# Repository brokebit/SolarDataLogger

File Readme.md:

# This repo has submodules
- To clone: git clone --recurse-submodules -j8 REPO_URL
- To pull latest versin: git pull --recurse-submodules

# What is all this

Firmware for custom data logger for Victron MPPT charge controllers via the Ve.Direct port/protocol.

## Features
- Power via 9v-20v input or USB
- ESP32-C6 RISC-V CPU
- Wifi 6 support and provisioning credentials via BLE
- Receive, parse, and publish data from a Victron MPPT controller
- Publishes: panel voltage, battery voltage, panel current, battery current, serial number, etc
- Publish data via MQTT in InfluxDB line protocol format
- Onboard temperature and humidity sensors (AHT20)
- Support for optional add on board with current sensor (INA226) and solid state relay (CMX60D10)
- WS2812 LED for status information
- CP2102N USB Uart for programing and logging
- USB port direct to ESP32-C6
- Remote control via MQTT command channel

## Supported Victron MPPT Controllers

Supports both the smaller MPPT controllers that have load output and control:

- MPPT 75/10
- MPPT 75/15
- MPPT 100/10
- MPPT 100/20

Also support larger MPPT controllers without load output via a INA226 Current sensor on an add-on board:

- MPPT 100/30
- MPPT 100/50
- MPPT 150/35
- MPPT 150/45
- MPPT 150/60
- MPPT 250/70

## The Details
This is a Platform IO project. Last tested with ESP IDF 5.3.1

- /lib contains drivers and victron parser
- /src contains main program

Edit platform.ini to set some global variables and config parameters. 
- INA226_PRESENT: Set this to one if you have a INA226 connected. Otherwise 0. 
- AHT20_PRESENT: Set this to 1 if you have a AHT20 connected. Otherwise 0.
- SENSOR_LOCATION: Set this to any string you want. It will be included in the mqtt message. No more than 24 characters
- SENSOR_TYPE: Set this to whatever you want. i.e. ESP32-C6 or ESP32-S3. No more than 24 characters

# MQTT

## Channels
- Influx data is sent to MQTT_TOPIC
- Command should be submitted to the channel named mac address + "-cmd" i.e. FFEEDDCCBBAA-cmd 
- Commands responses are sent to the channel named mac address. i.e. FFEEDDCCBBAA

## Support remote MQTT Commands
- ota - Perform an OTA Update
- rbk - Roll back to previous version 
- rst - Reboot
- png - Get a pong back
- tmp - Get current temp in C
- hum - Get current humidity
- mem - Get free heap memory
- ver - Get firmware version

# OTA
- Firmware is download via https from any URL. The firmware looks for a file that is the mac address in all caps. 
- Firmware URL is defined in : OTA_BASE_URL (without the filename)
- Rememeber you need to configure partitions.csv 1mb partition is not enough. 

# WiFi Provisioning
- To make a QR Code for provisioning use the following JSON string and fill in appropriate values:
```{"ver":"v1","name":"PROV_123456","pop":"abcd12345","transport":"ble"}```
- Use the mobile app called "ESP BLE Provisioning"
- In menuconfig make sure that: Component config -> Bluetooth -> Bluetooth controller -> Controller Options is set to BLE not Dual Mode.

# What can you do with it? 

## Grafana Dashboard Example

# To Do
- Fix math for INA226 current sensor and address twos compliment
- CMX60D10 Relay Driver
- Some way to configure it without recompiling 
- Redo design in KiCad instead of EasyEDA and add to repo
- Finish add onboard with INA226 and CMX60D10
- Code clean up. Comments, proper error handling, review memory managment, null point checks, etc
- Add remote commands for reading voltage and current data
- MQTT TLS Support

# Done
- WS2812 Driver
- OTA Updates
- Wifi Provisioning via BLE

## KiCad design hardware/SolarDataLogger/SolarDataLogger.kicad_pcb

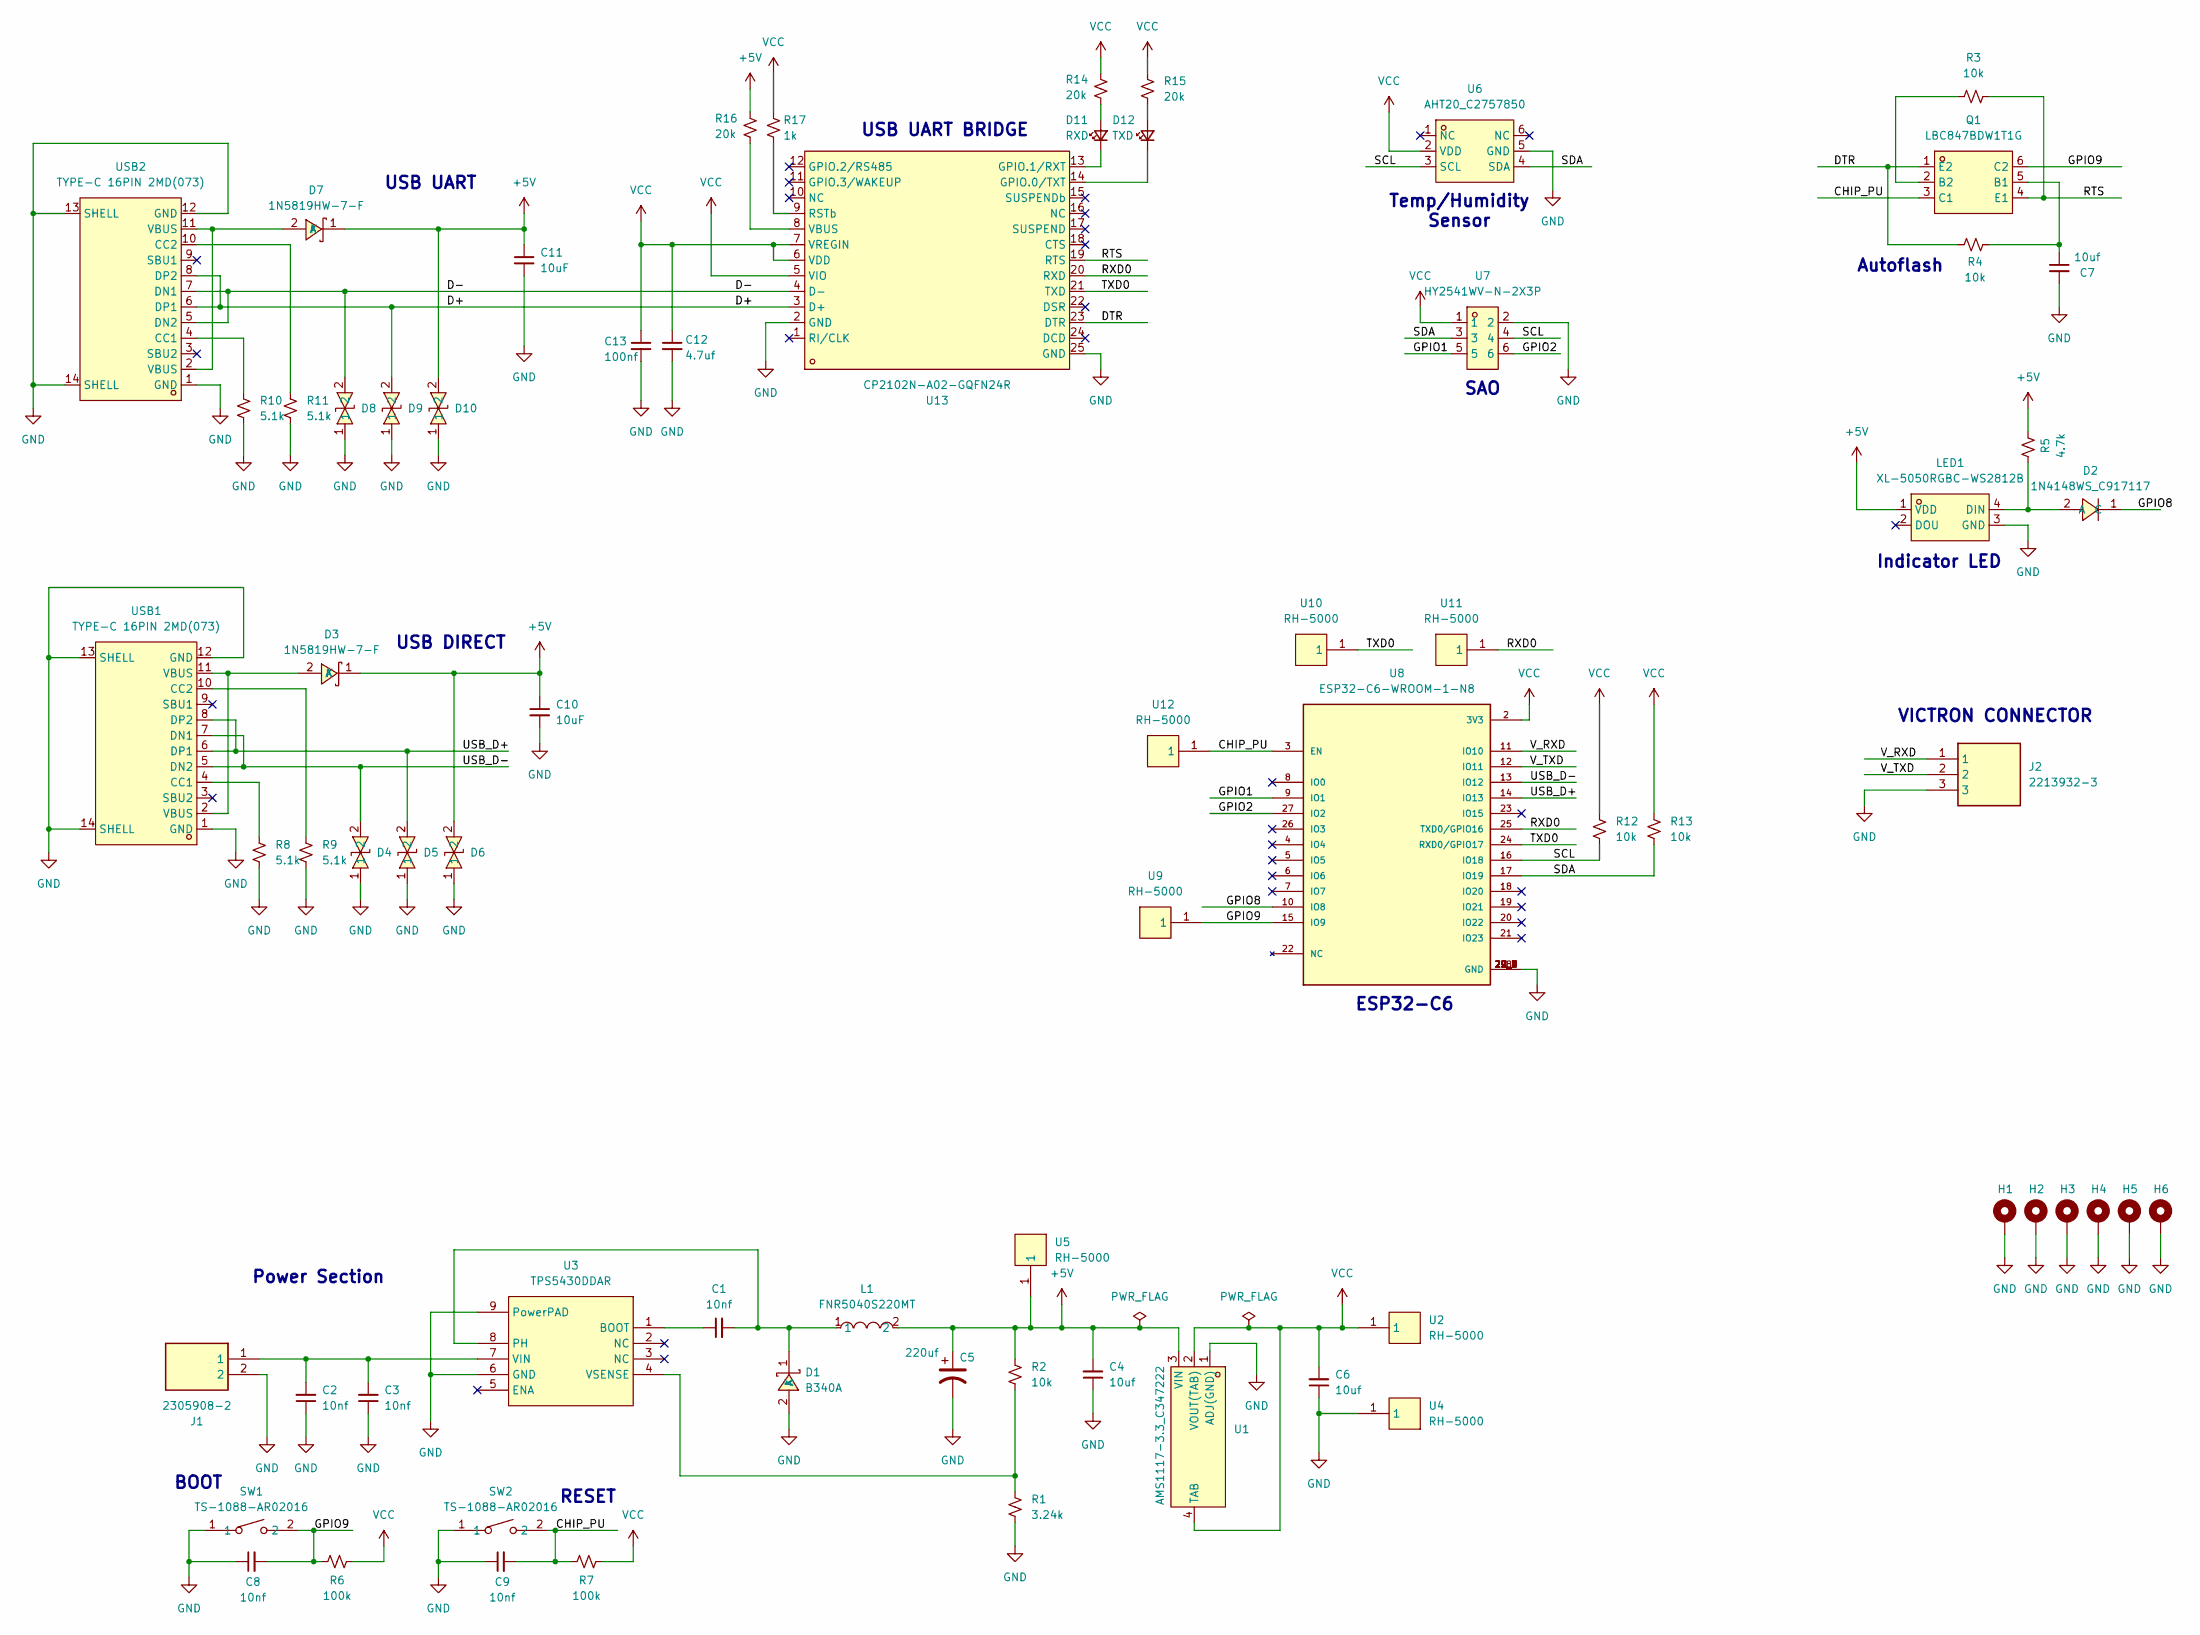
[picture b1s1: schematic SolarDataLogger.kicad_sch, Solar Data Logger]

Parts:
C1, C2, C3, C8, C9: 10nf; C_0603_1608Metric
C4, C6, C7: 10uf; C_0603_1608Metric
C5: 220uf; CAP-SMD_BD10.0-L10.3-W10.3-LS11.3-FD
C10, C11: 10uF; C_0603_1608Metric
C12: 4.7uf; C_0603_1608Metric
C13: 100nf; C_0603_1608Metric
D1: B340A; SMA_L4.3-W2.6-LS5.1-RD; LCSC Part C64982
D2: 1N4148WS_C917117; SOD-323_L1.8-W1.3-LS2.5-RD; LCSC Part C917117
D3, D7: 1N5819HW-7-F; SOD-123_L2.7-W1.6-LS3.7-RD; LCSC Part C82544
D4, D5, D6, D8, D9, D10: LESD5D5.0CT1G; SOD-523_L1.2-W0.8-LS1.6-BI; LCSC Part C383211
D11: RXD; LED_0603_1608Metric
D12: TXD; LED_0603_1608Metric
H1, H2, H3, H4, H5, H6: MountingHole_Pad; MountingHole_3.5mm_Pad_TopBottom
J1: 2305908-2; 23059082; Mouser Part Number 571-2305908-2
J2: 2213932-3; 22139323; Mouser Part Number 571-2213932-3
L1: FNR5040S220MT; IND-SMD_L5.0-W5.0; LCSC Part C167971
LED1: XL-5050RGBC-WS2812B; LED-SMD_4P-L5.0-W5.0-BL_XL-5050RGBC; LCSC Part C2843785
Q1: LBC847BDW1T1G; SOT-363_L2.0-W1.3-P0.65-LS2.1-BR; LCSC Part C383191
R1: 3.24k; R_0603_1608Metric
R2, R3, R4, R12, R13: 10k; R_0603_1608Metric
R5: 4.7k; R_0603_1608Metric
R6, R7: 100k; R_0603_1608Metric
R8, R9, R10, R11: 5.1k; R_0603_1608Metric
R14, R15, R16: 20k; R_0603_1608Metric
R17: 1k; R_0603_1608Metric
SW1, SW2: TS-1088-AR02016; SW-SMD_L3.9-W3.0-P4.45; LCSC Part C720477
U1: AMS1117-3.3_C347222; SOT-223-4_L6.5-W3.5-P2.30-LS7.0-BR; LCSC Part C347222
U2, U4, U5, U9, U10, U11, U12: RH-5000; TEST-TH_BD2.54-P1.4_RED; LCSC Part C5277086
U3: TPS5430DDAR; ESOP-8_L4.9-W3.9-P1.27-LS6.0-TL-EP; LCSC Part C9864
U6: AHT20_C2757850; SENSOR-SMD_L3.0-W3.0-P1.00-BR; LCSC Part C2757850
U7: HY2541WV-N-2X3P; IDC-Header_2x03_P2.54mm_Vertical_SMD; LCSC Part C17179450
U8: ESP32-C6-WROOM-1-N8; XCVR_ESP32-C6-WROOM-1-N8; PARTREV 1.0
U13: CP2102N-A02-GQFN24R; QFN-24_L4.0-W4.0-P0.50-TL-EP2.6; LCSC Part C969151
USB1, USB2: TYPE-C 16PIN 2MD(073); USB-C-SMD_TYPE-C-6PIN-2MD-073; LCSC Part C2765186

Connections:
+5V: C4.2, C5.1, C10.1, C11.1, D3.1 (K), D6.2, D7.1 (K), D10.2, L1.2, LED1.1 (VDD), R2.1, R5.1, R16.1, U1.3 (VIN), U5.1
/CHIP_PU: C9.2, Q1.3 (C1), R7.1, SW2.2, U8.3 (EN), U12.1
/D+: D9.2, U13.3 (D+), USB2.6 (DP1), USB2.8 (DP2)
/D-: D8.2, U13.4 (D-), USB2.5 (DN2), USB2.7 (DN1)
/DTR: Q1.1 (E2), R4.2, U13.23 (DTR)
/GPIO1: U7.5, U8.9 (IO1)
/GPIO2: U7.6, U8.27 (IO2)
/GPIO8: D2.1 (C), U8.10 (IO8)
/GPIO9: C8.2, Q1.6 (C2), R6.1, SW1.2, U8.15 (IO9), U9.1
/RTS: Q1.4 (E1), R3.2, U13.19 (RTS)
/RXD0: U8.25 (TXD0/GPIO16), U11.1, U13.20 (RXD)
/SCL: R12.1, U6.3 (SCL), U7.4, U8.16 (IO18)
/SDA: R13.1, U6.4 (SDA), U7.3, U8.17 (IO19)
/TXD0: U8.24 (RXD0/GPIO17), U10.1, U13.21 (TXD)
/USB_D+: D5.2, U8.14 (IO13), USB1.6 (DP1), USB1.8 (DP2)
/USB_D-: D4.2, U8.13 (IO12), USB1.5 (DN2), USB1.7 (DN1)
/V_RXD: J2.1, U8.11 (IO10)
/V_TXD: J2.2, U8.12 (IO11)
GND: C2.1, C3.1, C4.1, C5.2, C6.1, C7.2, C8.1, C9.1, C10.2, C11.2, C12.2, C13.2, D1.2 (A), D4.1, D5.1, D6.1, D8.1, D9.1, D10.1, H1.1, H2.1, H3.1, H4.1, H5.1, H6.1, J1.2, J2.3, LED1.3 (GND), R1.2, R8.2, R9.2, R10.2, R11.2, SW1.1, SW2.1, U1.1 (ADJ(GND)), U3.6 (GND), U3.9 (PowerPAD), U4.1, U6.5 (GND), U7.2, U8.1 (GND), U8.28 (GND), U8.29_1 (GND), U8.29_2 (GND), U8.29_3 (GND), U8.29_4 (GND), U8.29_5 (GND), U8.29_6 (GND), U8.29_7 (GND), U8.29_8 (GND), U8.29_9 (GND), U13.2 (GND), U13.25 (GND), USB1.1 (GND), USB1.12 (GND), USB1.13 (SHELL), USB1.14 (SHELL), USB2.1 (GND), USB2.12 (GND), USB2.13 (SHELL), USB2.14 (SHELL)
unnamed: C1.2, D1.1 (K), L1.1, U3.8 (PH)
unnamed: D2.2 (A), LED1.4 (DIN), R5.2
unnamed: D3.2 (A), USB1.2 (VBUS), USB1.11 (VBUS)
unnamed: D7.2 (A), USB2.2 (VBUS), USB2.11 (VBUS)
unnamed: D11.2 (A), R14.2
unnamed: D11.1 (K), U13.13 (GPIO.1/RXT)
unnamed: D12.2 (A), R15.2
unnamed: D12.1 (K), U13.14 (GPIO.0/TXT)
unnamed: C7.1, Q1.5 (B1), R4.1
unnamed: Q1.2 (B2), R3.1
unnamed: C1.1, U3.1 (BOOT)
unnamed: C2.2, C3.2, J1.1, U3.7 (VIN)
unnamed: R1.1, R2.2, U3.4 (VSENSE)
unnamed: R17.2, U13.9 (RSTb)
unnamed: R16.2, U13.8 (VBUS)
unnamed: R8.1, USB1.4 (CC1)
unnamed: R9.1, USB1.10 (CC2)
unnamed: R10.1, USB2.4 (CC1)
unnamed: R11.1, USB2.10 (CC2)
VCC: C6.2, C12.1, C13.1, R6.2, R7.2, R12.2, R13.2, R14.1, R15.1, R17.1, U1.2 (VOUT(TAB)), U1.4 (TAB), U2.1, U6.2 (VDD), U7.1, U8.2 (3V3), U13.5 (VIO), U13.6 (VDD), U13.7 (VREGIN)

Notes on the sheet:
Power Section
Indicator LED
USB UART BRIDGE
SAO
USB DIRECT
USB UART
VICTRON CONNECTOR
ESP32-C6
RESET
BOOT
Autoflash
Temp/Humidity Sensor

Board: 6 copper layers, 70 parts (0 on the bottom side), 39 nets, no tracks yet.

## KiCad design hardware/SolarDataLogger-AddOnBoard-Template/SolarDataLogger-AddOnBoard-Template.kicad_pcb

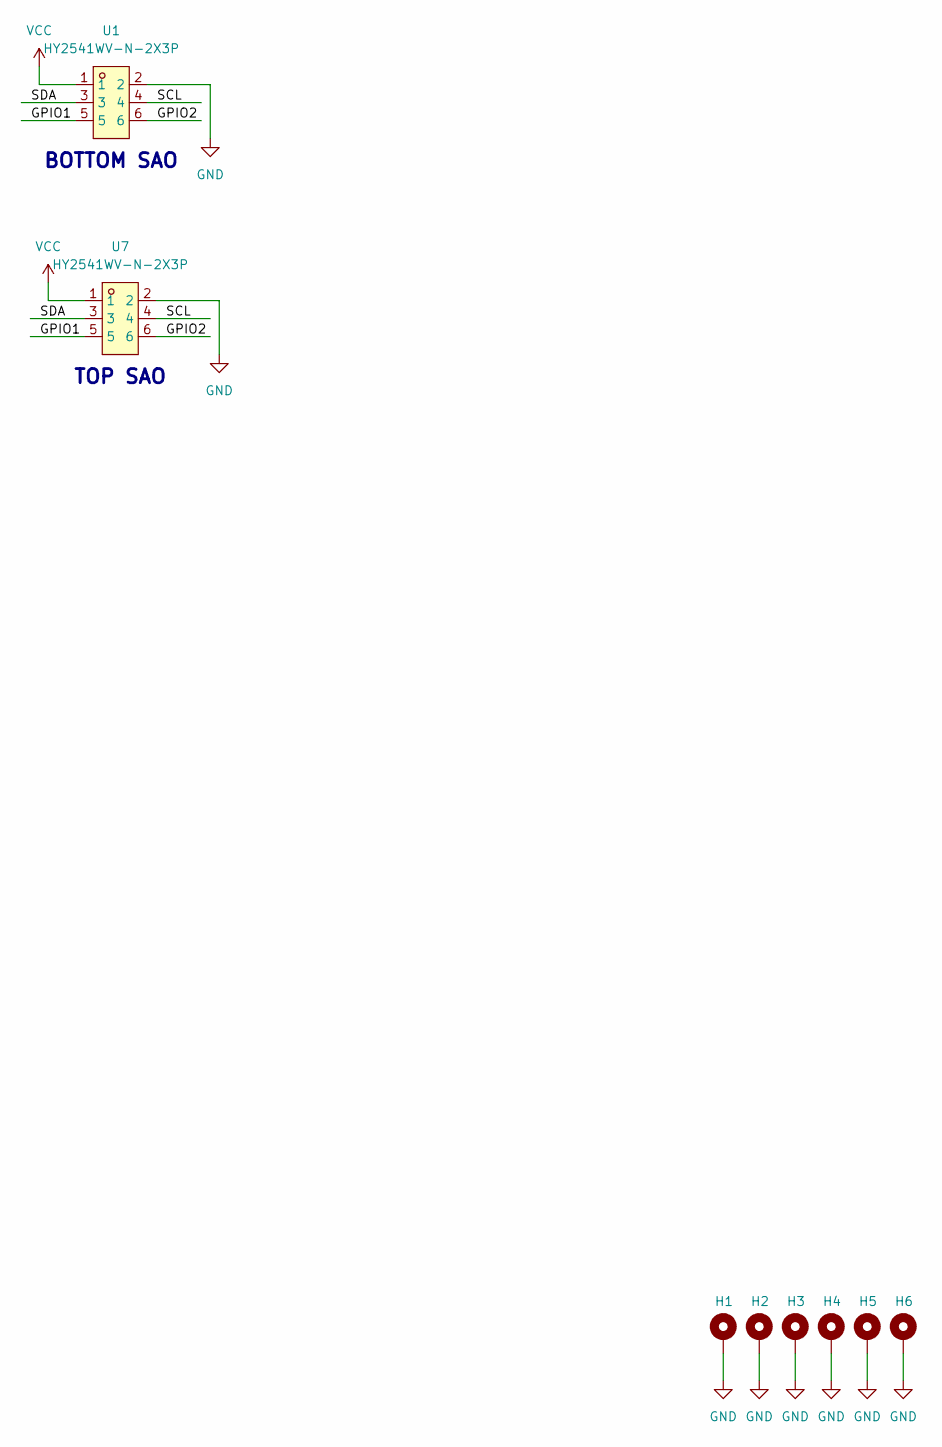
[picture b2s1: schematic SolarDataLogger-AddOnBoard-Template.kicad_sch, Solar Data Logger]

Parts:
H1, H2, H3, H4, H5, H6: MountingHole_Pad; MountingHole_3.5mm_Pad_TopBottom
U1: HY2541WV-N-2X3P; PinSocket_2x03_P2.54mm_Vertical_SMD; LCSC Part C17179450
U7: HY2541WV-N-2X3P; IDC-Header_2x03_P2.54mm_Vertical_SMD; LCSC Part C17179450

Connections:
/GPIO1: U1.5, U7.5
/GPIO2: U1.6, U7.6
/SCL: U1.4, U7.4
/SDA: U1.3, U7.3
GND: H1.1, H2.1, H3.1, H4.1, H5.1, H6.1, U1.2, U7.2
VCC: U1.1, U7.1

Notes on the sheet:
TOP SAO
BOTTOM SAO

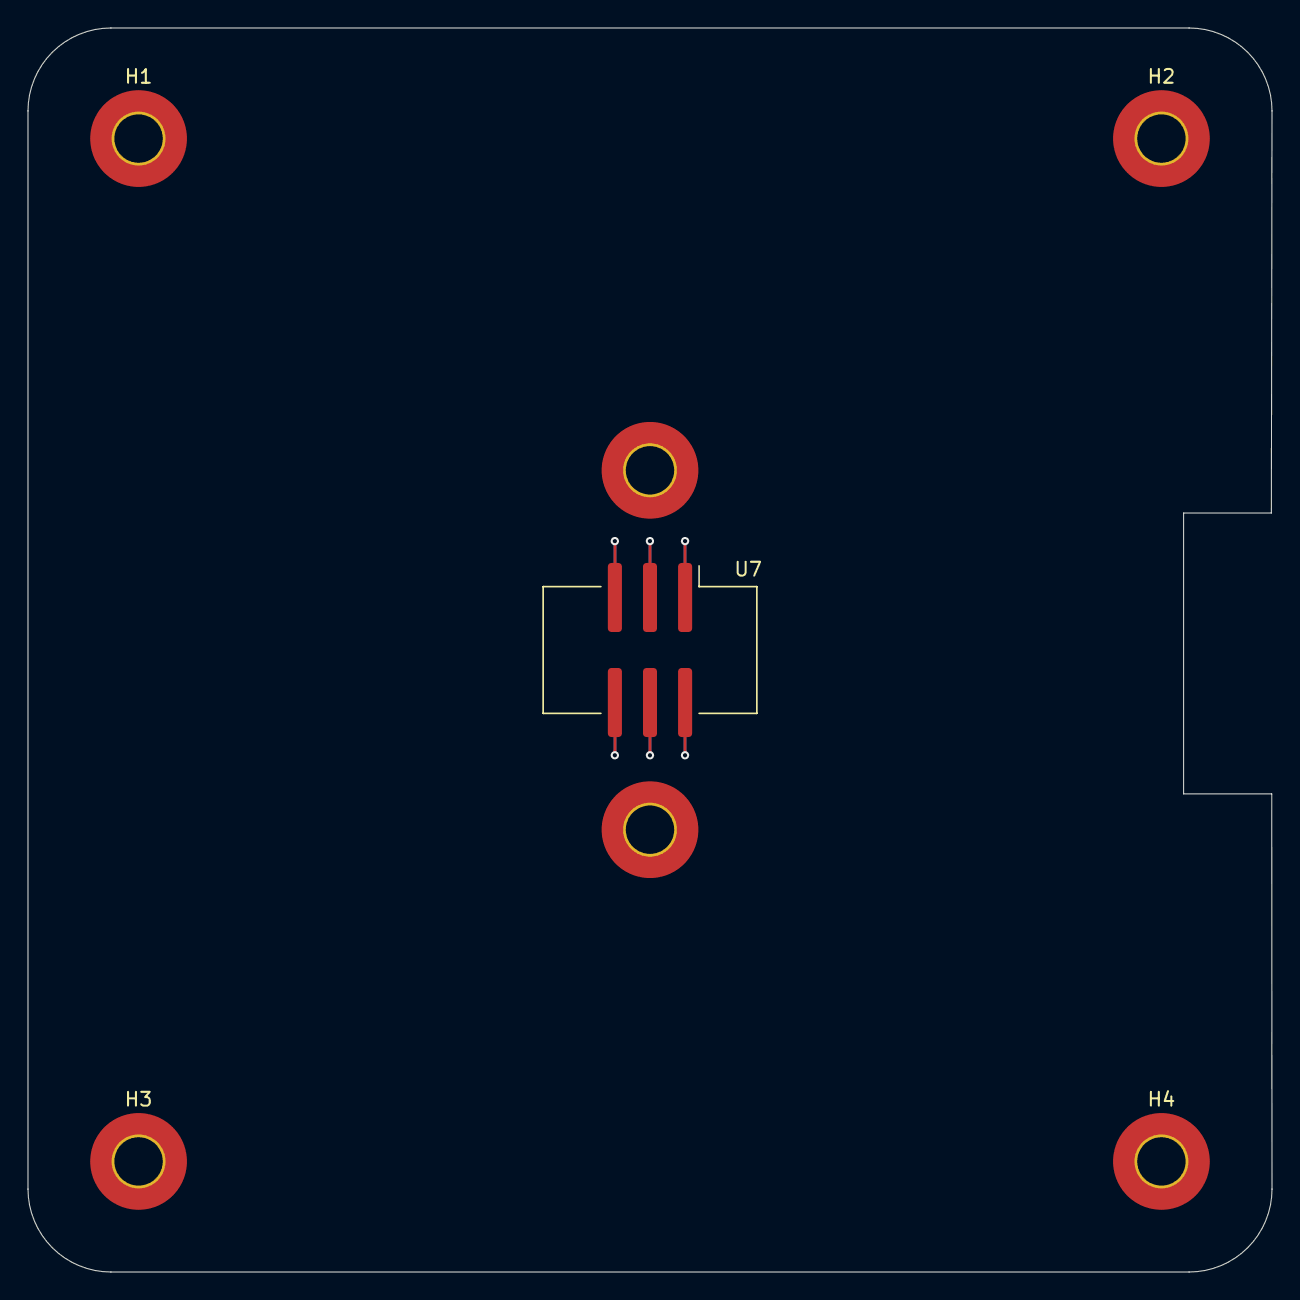
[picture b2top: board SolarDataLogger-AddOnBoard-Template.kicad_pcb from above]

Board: 6 copper layers, 90.0 x 90.0 mm, 8 parts (1 on the bottom side), 6 nets.

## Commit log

2025-01-19 Just busy work for the absurd
2025-01-19 A logo is needed
2025-01-19 Logos cause logos
2025-01-19 Cause spelling and words
2025-01-20 Migrating to KiCad Manually
2025-01-20 Moving along
2025-01-20 What?
2025-01-20 Add WS28xx driver as a git submodule
2025-01-20 Removed the esp_ws28xx submodule in favor of my fork
2025-01-20 Clean up my mess
2025-01-20 Adding my forked copy
2025-01-20 Increase partition sizes. Add LED driver and code
2025-01-20 Update schematic because I wanted to
2025-01-20 Update background
2025-01-21 The work must be done
2025-01-21 Ideas
2025-01-21 Templates for all!
2025-01-23 Color is better than no color
2025-01-23 Misc clean up because birds aren't real
2025-01-23 Working OTA cause Suki told me to
2025-01-23 Spock requires kibble
2025-01-23 Refactor cause it's the X factor
2025-01-24 Null pointer checks are for babies.
2025-01-24 the feeling of progress is just a feeling
2025-01-24 I'm a baby
2025-01-24 The journey is long. It's always long.
2025-01-24 I command you
2025-01-25 Remember what you are doing
2025-01-25 Provincial Provisioning for the providers
2025-01-25 Readyou.md
2025-01-26 Wiat for it
2025-02-10 Working on stuff
2025-02-14 It's raining a lot
2025-02-17 What time is your haircut?
2025-02-17 Oops
